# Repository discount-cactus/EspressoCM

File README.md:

# EspressoCM
Espresso Rev 4 CM, or just Espresso CM, is an STM32- and ESP32-based compute module for high performance networking and automation applications. The board was designed to provide a plethora of capabilities in a small, user-friendly and cheap package. An STM32 and two (not one but two!) ESP32's were chosen for their ease-of-use, clock speed and peripherals to acommodate these requirements. For the beginner or novel hobbyist, the ESP32's can be used - both come with their own dedicated flash memory chip as well as Wi-Fi and Bluetooth connectivity. For the more advanced and tech-savy, the STM32 can be programmed directly for higher-performance control.

Link to EspressoCM's complimentary library: https://github.com/discount-cactus/EspressoCMlib

## Board Statistics
- Dimensions: 84.9mm x 50.2mm
- Layers: 4
- Components: 83
- Mounting Hole Size: M2

## Features
- 1 x STM32F107 (@72MHz)
- 2 x ESP32-S3 (@240MHz)
- 1 x ATtiny85
- 1.5A linear regulator (VIN: 3-20V)
- Automatic power switchover from terminal block `J7` and JST battery connector `J8`
- JST LiPo Battery Connector
- 128Mbit Flash (one per ESP32)
- Dedicated E2B functionality
- On-board current sensing

## Applications
- Smart Homes
- Home networks
- IoT Connectivity
- Home automation
- Sensor monitoring

## Programming
### STM32
- The STM32 is programmed on-board via the pin connector `J5` with an ST-Link V2.
- Verify STM32CubeIDE is up-to-date
- Verify ST-Link V2 is up-to-date
1. Set BOOT0 to HIGH
2. Push reset button
3. Build code
4. Run code
5. Set BOOT0 to LOW
6. Push reset button

### ESP32
- The ESP32's are programmed on-board via the header pins `J3` (for Core 1) and `J4` (for Core 2). Pins are labeled on silkscreen.

### ATtiny85
- The ATtiny85 is programmed off-board.

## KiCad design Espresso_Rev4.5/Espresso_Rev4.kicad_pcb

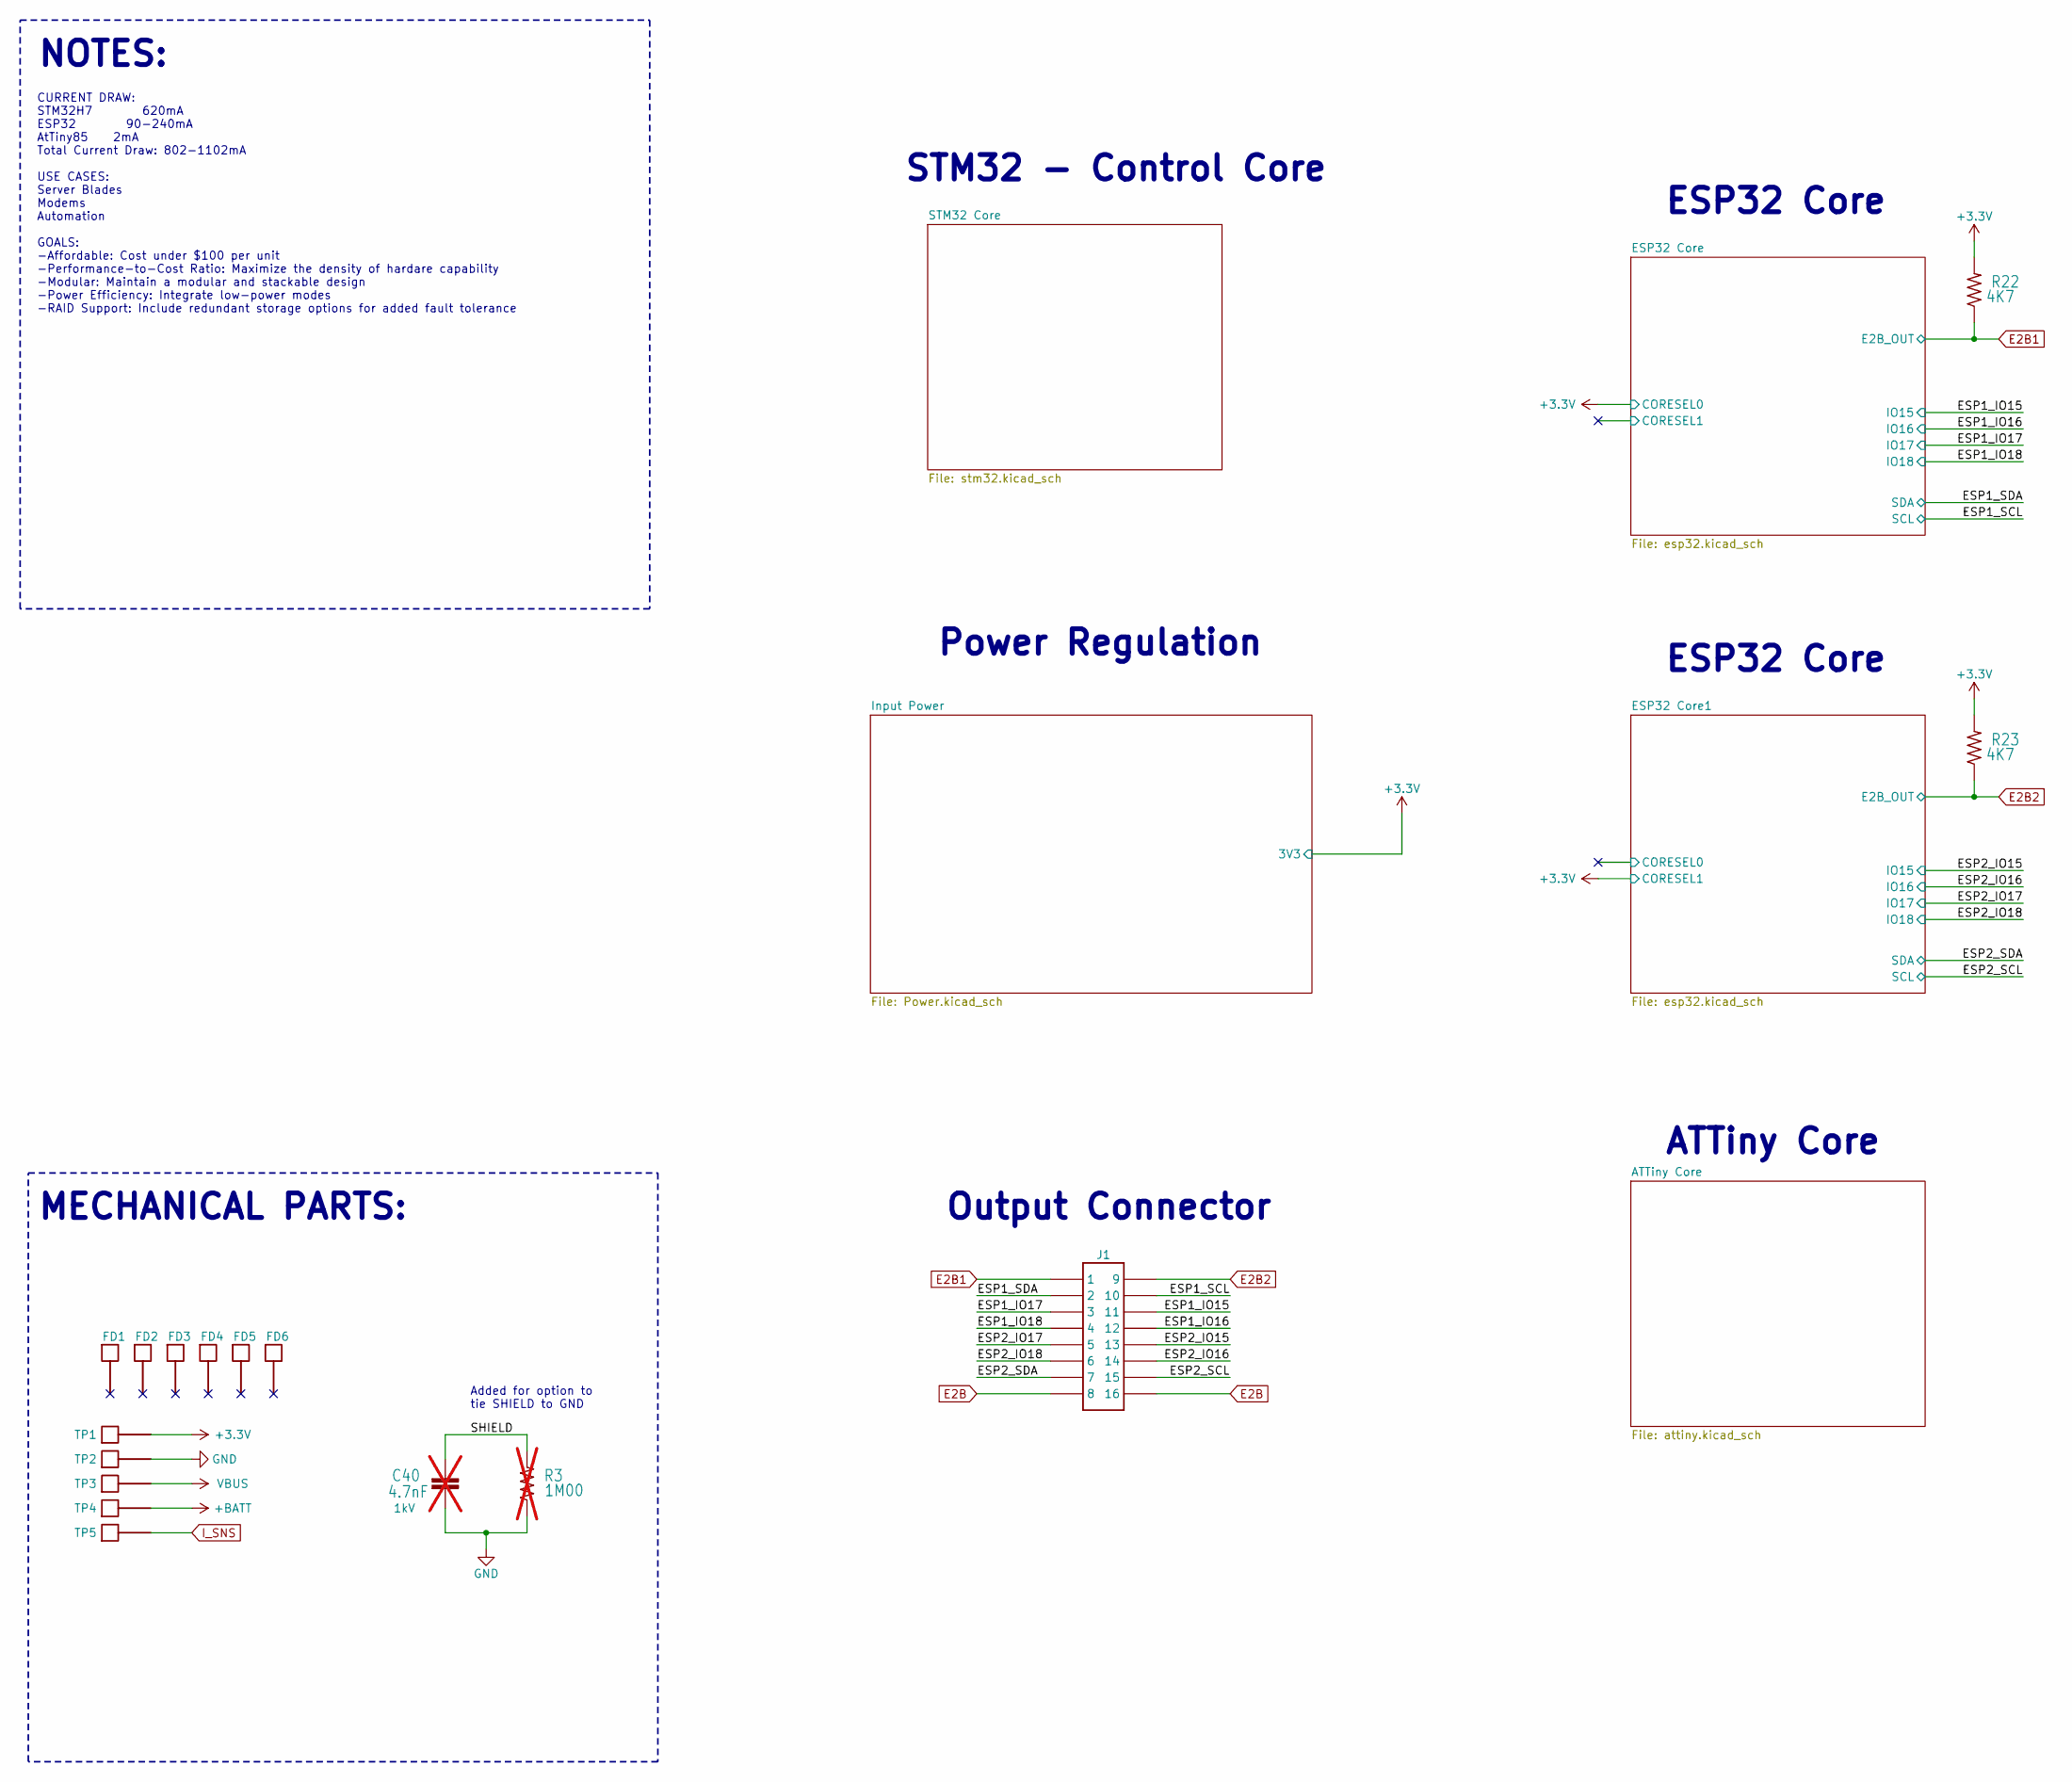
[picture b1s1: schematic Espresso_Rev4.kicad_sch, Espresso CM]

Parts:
C40: 4.7nF; C_1206; Rating 1kV; Part Number C1206C472KDRACAUTO; not fitted
FD1, FD2, FD3, FD4, FD5, FD6: Fiducial_1.5mm_Mask3mm
J1: 2X8; Part Number PPTC082LJBN-RC
R3: 1M00; R_1206; Rating 1/4W; Part Number RMCF1206FG1M00; not fitted
R22, R23: 4K7; R_1206; Rating 1/4W; Part Number RMCF1206FT4K70
TP1, TP2, TP3, TP4, TP5: TESTPOINT

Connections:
+3.3V: R22.2, R23.2, TP1.1; also elsewhere on the board
+BATT: TP4.1; also elsewhere on the board
/ESP1_IO15: J1.11; also elsewhere on the board
/ESP1_IO16: J1.12; also elsewhere on the board
/ESP1_IO17: J1.3; also elsewhere on the board
/ESP1_IO18: J1.4; also elsewhere on the board
/ESP1_SCL: J1.10; also elsewhere on the board
/ESP1_SDA: J1.2; also elsewhere on the board
/ESP2_IO15: J1.13; also elsewhere on the board
/ESP2_IO16: J1.14; also elsewhere on the board
/ESP2_IO17: J1.5; also elsewhere on the board
/ESP2_IO18: J1.6; also elsewhere on the board
/ESP2_SCL: J1.15; also elsewhere on the board
/ESP2_SDA: J1.7; also elsewhere on the board
/SHIELD: C40.1, R3.2; also elsewhere on the board
E2B: J1.8, J1.16; also elsewhere on the board
E2B1: J1.1, R22.1; also elsewhere on the board
E2B2: J1.9, R23.1; also elsewhere on the board
GND: C40.2, R3.1, TP2.1; also elsewhere on the board
I_SNS: TP5.1; also elsewhere on the board
VBUS: TP3.1; also elsewhere on the board

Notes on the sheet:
MECHANICAL PARTS:
Power Regulation
Added for option to tie SHIELD to GND
Output Connector
ESP32 Core
NOTES:
CURRENT DRAW: STM32H7 620mA ESP32 90-240mA AtTiny85 2mA Total Current Draw: 802-1102mA USE CASES: Server Blades Modems Automation GOALS: -Affordable: Cost under $100 per unit -Performance-to-Cost Ratio: Maximize the density of hardare capability -Modular: Maintain a modular and stackable design -Po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
ATTiny Core
STM32 - Control Core

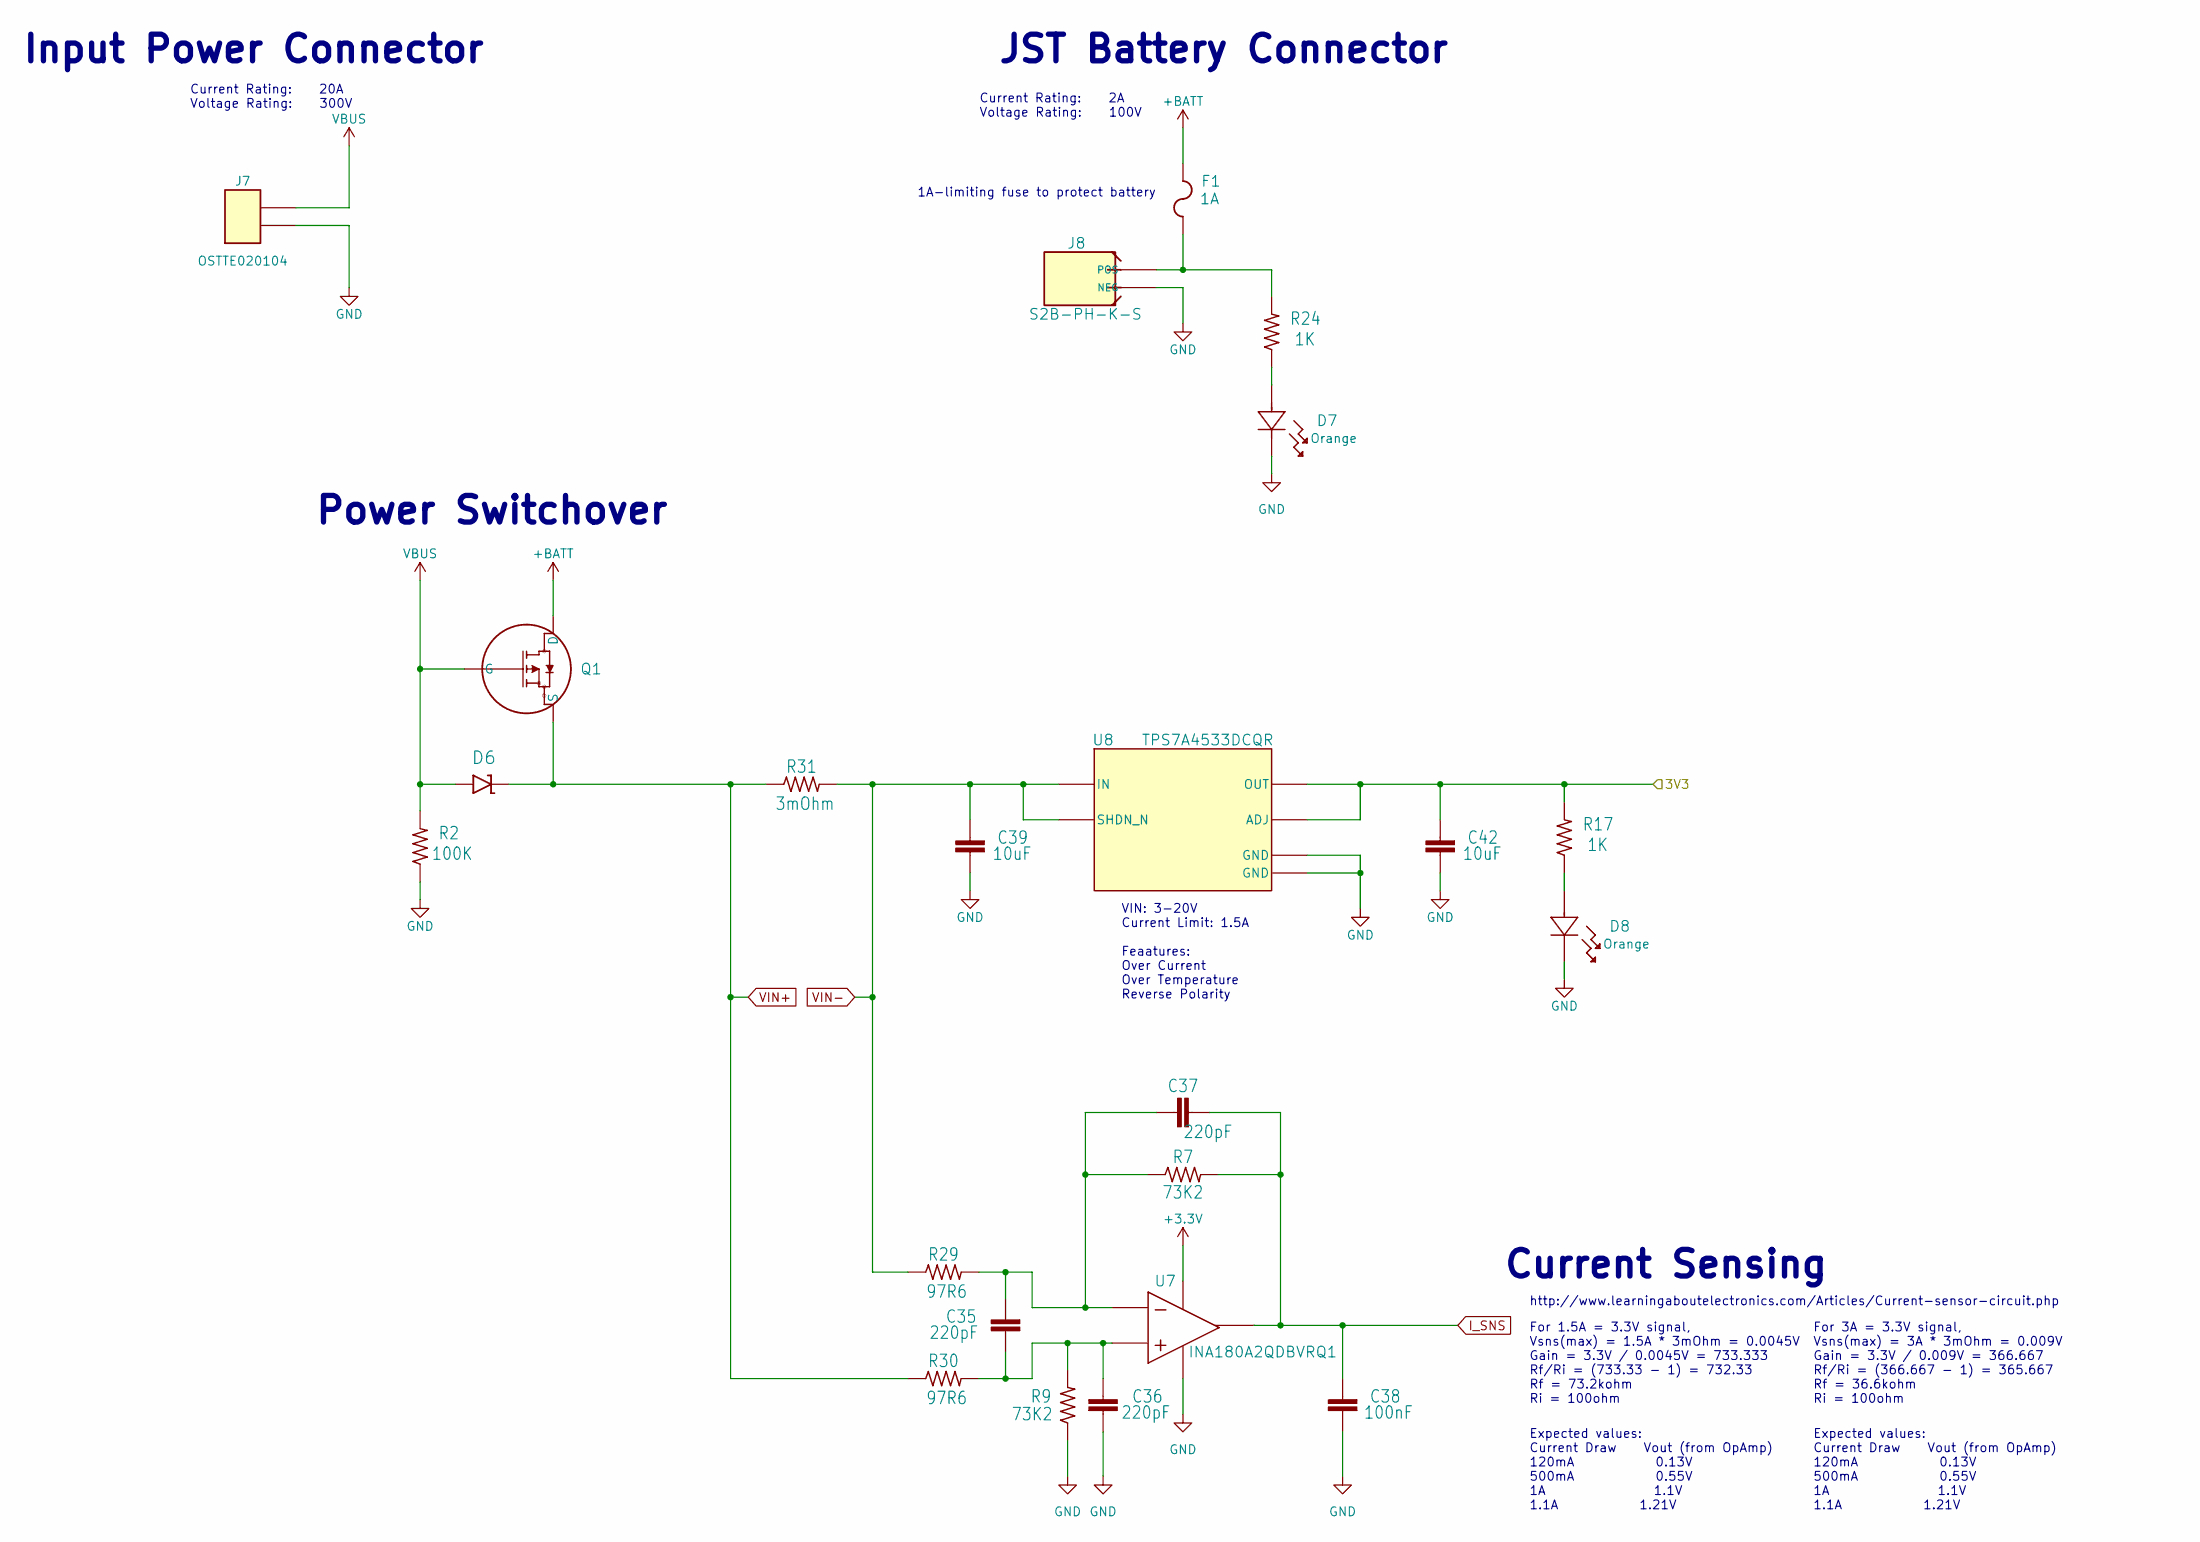
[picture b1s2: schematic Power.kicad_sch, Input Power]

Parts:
C35, C36, C37: 220pF; C_0603; Rating 50V; Part Number CL10B221KB8NFNC
C38: 100nF; C_0603; Rating 50V; Part Number CL10B104KB8NNNC
C39, C42: 10uF; C_0603; Rating 25V; Part Number CL10A106MA8NRNC
D6: SK54AHE3-LTP; Part Number SK54AHE3-LTP
D7, D8: LED_0603; Part Number LTST-C191KFKT
F1: 1A; MF-FSMF050X-2; Part Number MF-FSMF050X-2
J7: OSTTE020104; Rating 10A; Part Number OSTTE020104
J8: S2B-PH-K-S; Part Number S2B-PH-K-S
Q1: DMP3099L-7; Part Number DMP3099L-7
R2: 100K; R_0603; Rating 1/10W; Part Number RMCF0603FT100K
R7, R9: 73K2; R_0603; Rating 1/10W; Part Number RMCF0603FT73K2
R17, R24: 1K; R_0603; Rating 1/10W; Part Number RMCF0603FT1K00
R29, R30: 97R6; R_1206; Rating 1/4W; Part Number RK73H2BTTD97R6F
R31: 3mOhm; R_1206; Rating 1W; Part Number PMR18EZPFV3L00
U7: INA180A2QDBVRQ1; Part Number INA180A2QDBVRQ1
U8: TPS7A4533DCQR; Part Number TPS7A4533DCQR

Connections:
+3.3V: C42.2, R17.2, U7.5 (V+), U8.4 (OUT), U8.5 (ADJ); also elsewhere on the board
+BATT: F1.2, Q1.3 (D); also elsewhere on the board
GND: C36.1, C38.1, C39.1, C42.1, D7.1, D8.1, J7.1, J8.2 (NEG), R2.1, R9.1, U7.2 (V-), U8.3 (GND), U8.6 (GND); also elsewhere on the board
I_SNS: C37.2, C38.2, R7.2, U7.1 (OUT); also elsewhere on the board
unnamed: D7.2, R24.1
unnamed: D8.2, R17.1
unnamed: F1.1, J8.1 (POS), R24.2
unnamed: C35.1, C36.2, R9.2, R30.2, U7.3 (IN+)
unnamed: C35.2, C37.1, R7.1, R29.2, U7.4 (IN-)
VBUS: D6.2, J7.2, Q1.1 (G), R2.2; also elsewhere on the board
VIN+: D6.1, Q1.2 (S), R30.1, R31.1
VIN-: C39.2, R29.1, R31.2, U8.1 (SHDN_N), U8.2 (IN)

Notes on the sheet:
http://www.learningaboutelectronics.com/Articles/Current-sensor-circuit.php
VIN: 3-20V Current Limit: 1.5A Feaatures: Over Current Over Temperature Reverse Polarity
1A-limiting fuse to protect battery
Expected values: Current Draw Vout (from OpAmp) 120mA 0.13V 500mA 0.55V 1A 1.1V 1.1A 1.21V
For 1.5A = 3.3V signal, Vsns(max) = 1.5A * 3mOhm = 0.0045V Gain = 3.3V / 0.0045V = 733.333 Rf/Ri = (733.33 - 1) = 732.33 Rf = 73.2kohm Ri = 100ohm
Power Switchover
For 3A = 3.3V signal, Vsns(max) = 3A * 3mOhm = 0.009V Gain = 3.3V / 0.009V = 366.667 Rf/Ri = (366.667 - 1) = 365.667 Rf = 36.6kohm Ri = 100ohm
Current Rating: 2A Voltage Rating: 100V
Current Rating: 20A Voltage Rating: 300V
JST Battery Connector
Current Sensing
Input Power Connector

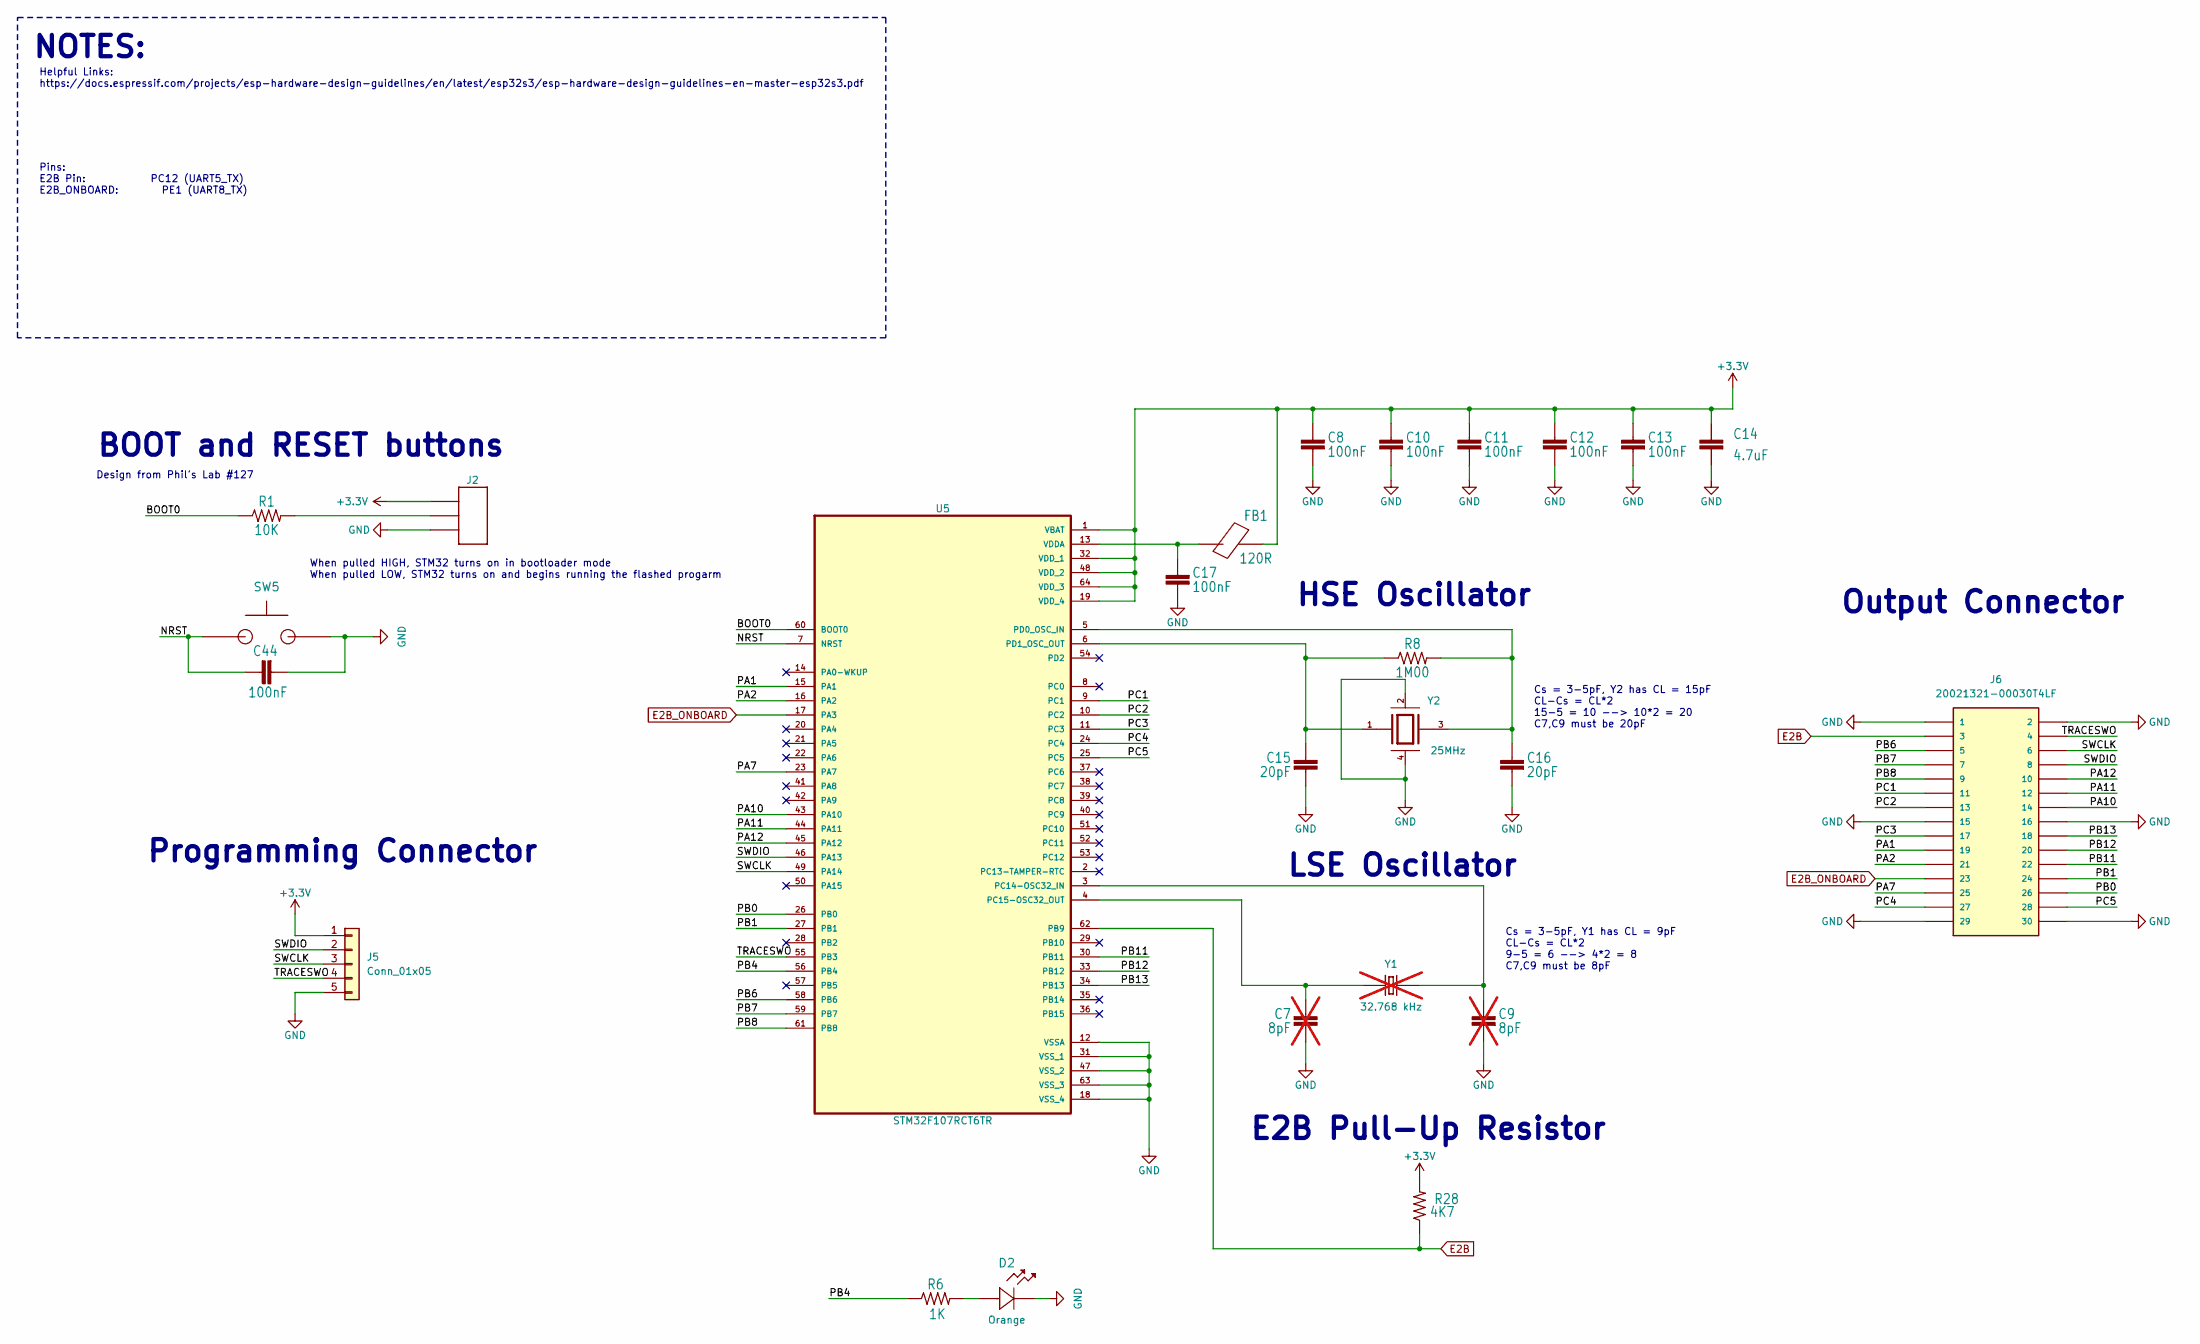
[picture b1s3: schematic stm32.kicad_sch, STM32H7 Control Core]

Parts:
C7, C9: 8pF; C_0603; Rating 50V; Part Number CL10C080DB81PNC; not fitted
C8, C10, C11, C12, C13, C17, C44: 100nF; C_0603; Rating 50V; Part Number CL10B104KB8NNNC
C14: 4.7uF; C_0603; Rating 25V; Part Number CL10A475MA8NQNC
C15, C16: 20pF; C_0603; Rating 50V; Part Number CL10C200JB8NNNC
D2: LED_0603; Part Number LTST-C191KFKT
FB1: 120R; FB_0603; Part Number BLM18KG121TN1D
J2: 1X3
J5: Conn_01x05; PinHeader_1x05_P2.54mm_Vertical
J6: 20021321-00030T4LF; Part Number 20021321-00030T4LF
R1: 10K; R_0603; Rating 1/10W; Part Number RMCF0603FT10K0
R6: 1K; R_0603; Rating 1/10W; Part Number RMCF0603FT1K00
R8: 1M00; R_0603; Rating 1/10W; Part Number RMCF0603FT1M00
R28: 4K7; R_1206; Rating 1/4W; Part Number RMCF1206FT4K70
SW5: PTS636 SK25J SMTR LFS; Part Number PTS636SK25JSMTR LFS
U5: STM32F107RCT6TR; Part Number STM32F107RCT6TR
Y1: 32.768 kHz; ECS-.327-9-34B-TR; Part Number ECS-.327-9-34B-TR; not fitted
Y2: 25MHz; ECS-2333-250-BN-TR; Part Number ECS-2333-250-BN-TR

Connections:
+3.3V: C8.2, C10.2, C11.2, C12.2, C13.2, C14.2, FB1.2, J2.1, J5.1, R28.2, U5.1 (VBAT), U5.19 (VDD_4), U5.32 (VDD_1), U5.48 (VDD_2), U5.64 (VDD_3); also elsewhere on the board
/STM32 Core/BOOT0: R1.1, U5.60 (BOOT0)
/STM32 Core/NRST: C44.2, SW5.1, U5.7 (NRST)
/STM32 Core/PA1: J6.19, U5.15 (PA1)
/STM32 Core/PA2: J6.21, U5.16 (PA2)
/STM32 Core/PA7: J6.25, U5.23 (PA7)
/STM32 Core/PA10: J6.14, U5.43 (PA10)
/STM32 Core/PA11: J6.12, U5.44 (PA11)
/STM32 Core/PA12: J6.10, U5.45 (PA12)
/STM32 Core/PB0: J6.26, U5.26 (PB0)
/STM32 Core/PB1: J6.24, U5.27 (PB1)
/STM32 Core/PB4: R6.1, U5.56 (PB4)
/STM32 Core/PB6: J6.5, U5.58 (PB6)
/STM32 Core/PB7: J6.7, U5.59 (PB7)
/STM32 Core/PB8: J6.9, U5.61 (PB8)
/STM32 Core/PB11: J6.22, U5.30 (PB11)
/STM32 Core/PB12: J6.20, U5.33 (PB12)
/STM32 Core/PB13: J6.18, U5.34 (PB13)
/STM32 Core/PC1: J6.11, U5.9 (PC1)
/STM32 Core/PC2: J6.13, U5.10 (PC2)
/STM32 Core/PC3: J6.17, U5.11 (PC3)
/STM32 Core/PC4: J6.27, U5.24 (PC4)
/STM32 Core/PC5: J6.28, U5.25 (PC5)
/STM32 Core/SWCLK: J5.3, J6.6, U5.49 (PA14)
/STM32 Core/SWDIO: J5.2, J6.8, U5.46 (PA13)
/STM32 Core/TRACESWO: J5.4, J6.4, U5.55 (PB3)
E2B: J6.3, R28.1, U5.62 (PB9); also elsewhere on the board
E2B_ONBOARD: J6.23, U5.17 (PA3); also elsewhere on the board
GND: C7.1, C8.1, C9.1, C10.1, C11.1, C12.1, C13.1, C14.1, C15.1, C16.1, C17.1, C44.1, D2.1, J2.3, J5.5, J6.1, J6.2, J6.15, J6.16, J6.29, J6.30, SW5.2, U5.12 (VSSA), U5.18 (VSS_4), U5.31 (VSS_1), U5.47 (VSS_2), U5.63 (VSS_3), Y2.2 (GND), Y2.4 (GND); also elsewhere on the board
unnamed: D2.2, R6.2
unnamed: J2.2, R1.2
unnamed: C9.2, U5.3 (PC14-OSC32_IN), Y1.2
unnamed: C7.2, U5.4 (PC15-OSC32_OUT), Y1.1
unnamed: C16.2, R8.2, U5.5 (PD0_OSC_IN), Y2.3 (OUT)
unnamed: C15.2, R8.1, U5.6 (PD1_OSC_OUT), Y2.1 (IN)
unnamed: C17.2, FB1.1, U5.13 (VDDA)

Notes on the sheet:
HSE Oscillator
E2B Pull-Up Resistor
Pins: E2B Pin: PC12 (UART5_TX) E2B_ONBOARD: PE1 (UART8_TX)
Design from Phil's Lab #127
Output Connector
NOTES:
When pulled HIGH, STM32 turns on in bootloader mode When pulled LOW, STM32 turns on and begins running the flashed progarm
LSE Oscillator
Cs = 3-5pF, Y2 has CL = 15pF CL-Cs = CL*2 15-5 = 10 --> 10*2 = 20 C7,C9 must be 20pF
Cs = 3-5pF, Y1 has CL = 9pF CL-Cs = CL*2 9-5 = 6 --> 4*2 = 8 C7,C9 must be 8pF
Programming Connector
BOOT and RESET buttons
Helpful Links: https://docs.espressif.com/projects/esp-hardware-design-guidelines/en/latest/esp32s3/esp-hardware-design-guidelines-en-master-esp32s3.pdf

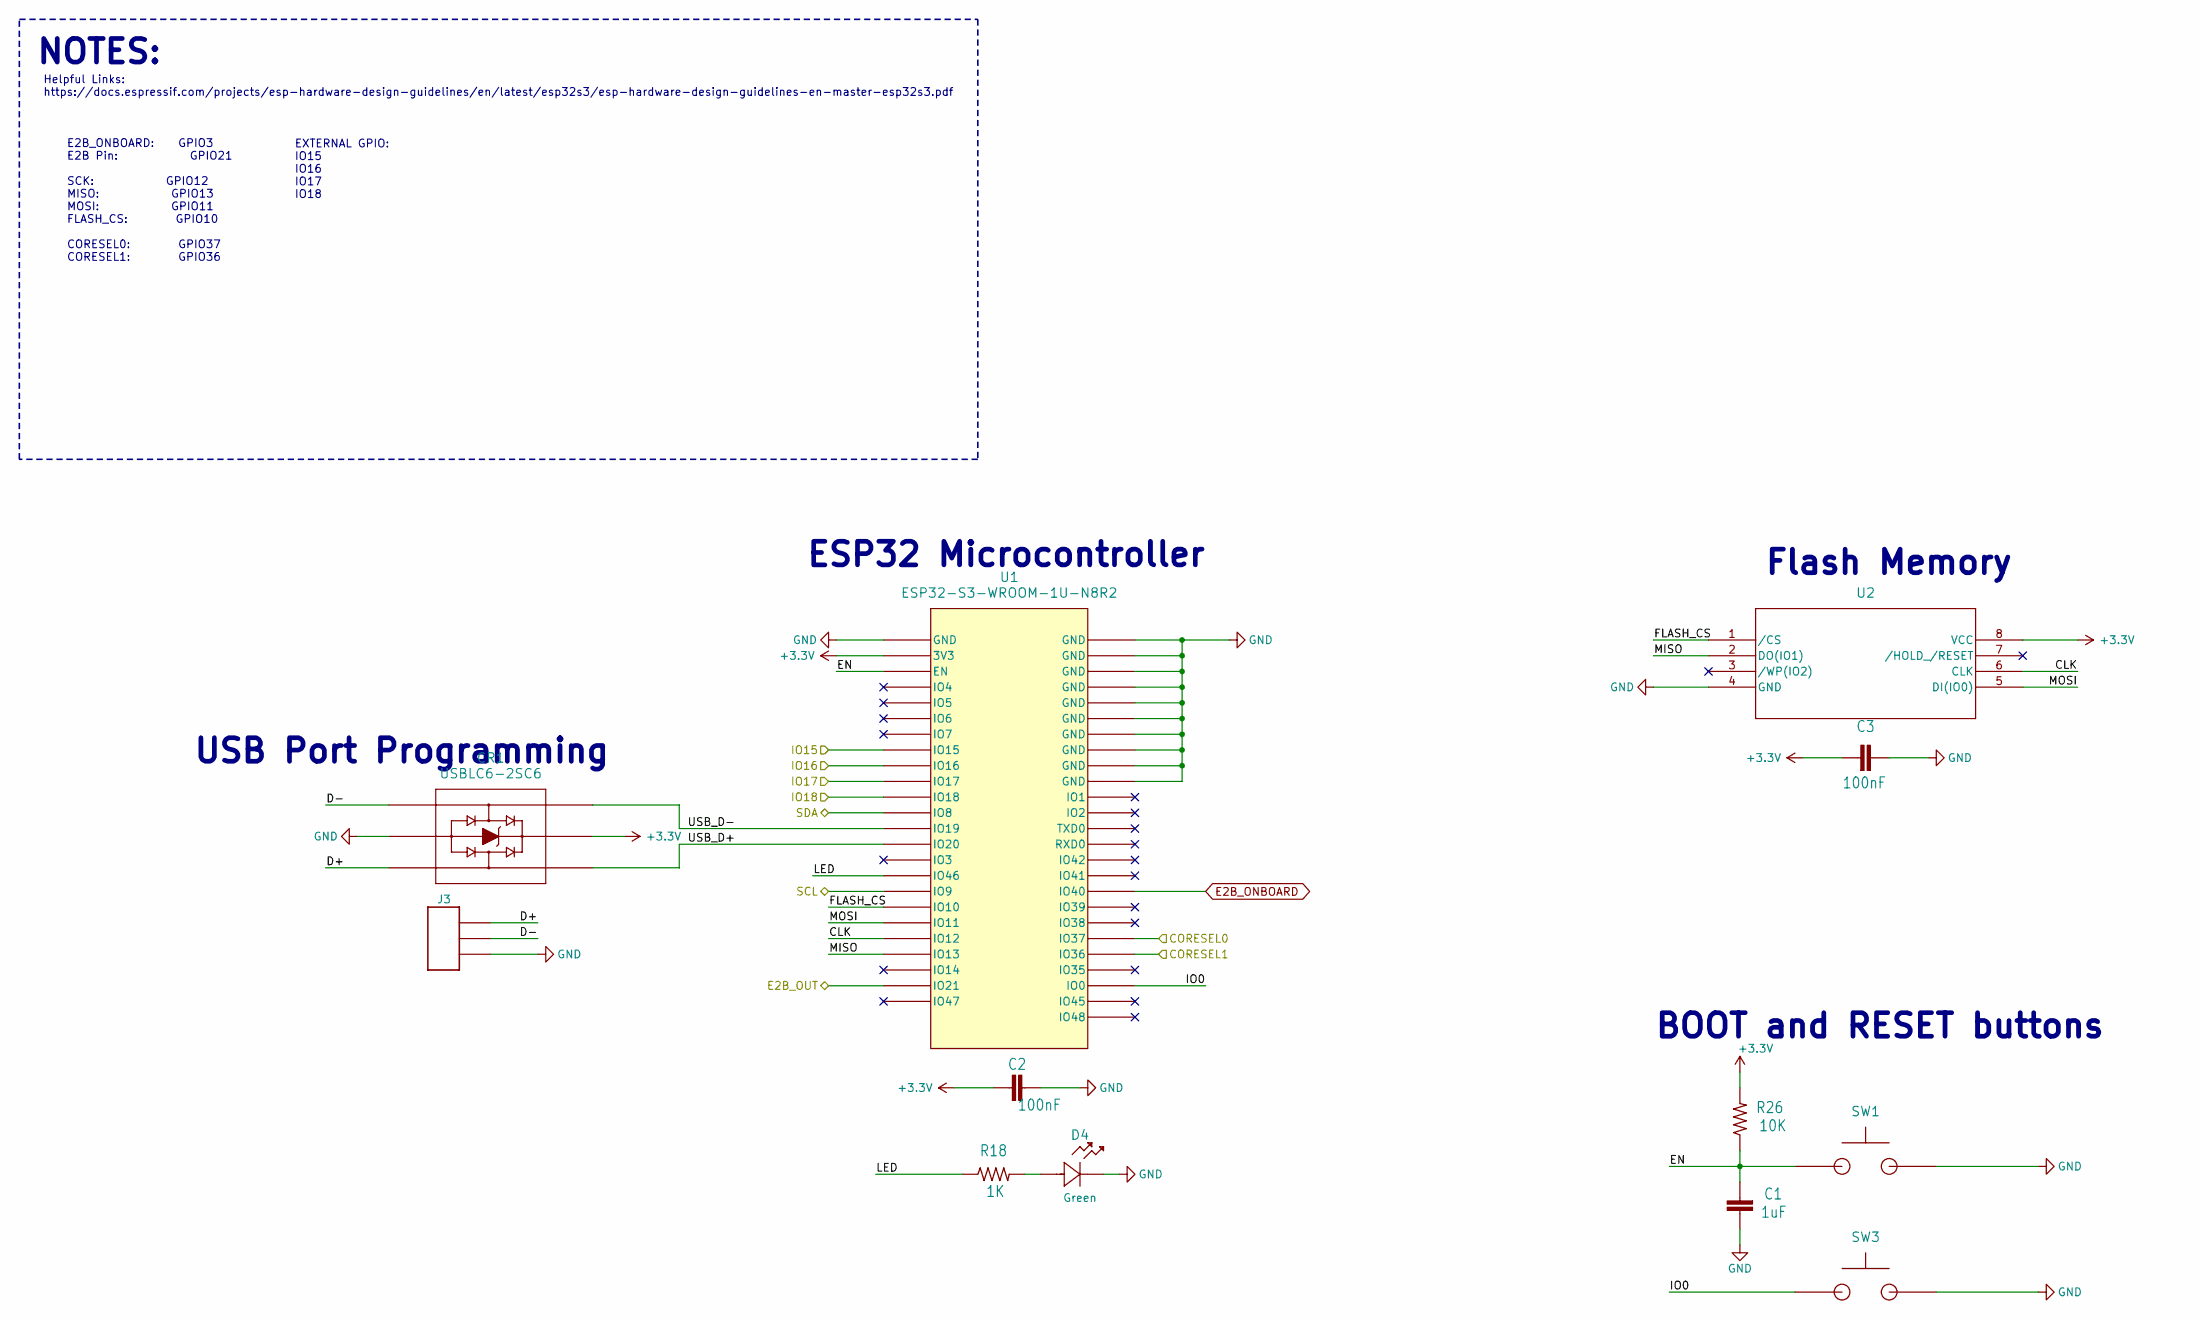
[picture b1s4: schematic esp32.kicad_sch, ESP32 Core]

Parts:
C1: 1uF; C_0603; Rating 50V; Part Number CL10A105KB8NNNC
C2, C3: 100nF; C_0603; Rating 50V; Part Number CL10B104KB8NNNC
CR1: USBLC6-2SC6; Part Number USBLC6-2SC6
D4: LED_0603; Part Number LTST-C191KGKT
J3: 1X3
R18: 1K; R_0603; Rating 1/10W; Part Number RMCF0603FT1K00
R26: 10K; R_0603; Rating 1/10W; Part Number RMCF0603FT10K0
SW1, SW3: PTS636 SK25J SMTR LFS; Part Number PTS636SK25JSMTR LFS
U1: ESP32-S3-WROOM-1U-N8R2; Part Number ESP32-S3-WROOM-1U-N8R2
U2: W25Q128JVSIQ; Part Number W25Q128JVSIQ

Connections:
+3.3V: C2.1, C3.1, CR1.5, R26.2, U1.2 (3V3), U1.30 (IO37), U2.8 (VCC); also elsewhere on the board
/ESP1_IO15: U1.8 (IO15); also elsewhere on the board
/ESP1_IO16: U1.9 (IO16); also elsewhere on the board
/ESP1_IO17: U1.10 (IO17); also elsewhere on the board
/ESP1_IO18: U1.11 (IO18); also elsewhere on the board
/ESP1_SCL: U1.17 (IO9); also elsewhere on the board
/ESP1_SDA: U1.12 (IO8); also elsewhere on the board
/ESP32 Core/CLK: U1.20 (IO12), U2.6 (CLK)
/ESP32 Core/CORESEL1: U1.29 (IO36)
/ESP32 Core/D+: CR1.3, J3.1
/ESP32 Core/D-: CR1.1, J3.2
/ESP32 Core/EN: C1.2, R26.1, SW1.1, U1.3 (EN)
/ESP32 Core/FLASH_CS: U1.18 (IO10), U2.1 (/CS)
/ESP32 Core/IO0: SW3.1, U1.27 (IO0)
/ESP32 Core/LED: R18.1, U1.16 (IO46)
/ESP32 Core/MISO: U1.21 (IO13), U2.2 (DO(IO1))
/ESP32 Core/MOSI: U1.19 (IO11), U2.5 (DI(IO0))
/ESP32 Core/USB_D+: CR1.4, U1.14 (IO20)
/ESP32 Core/USB_D-: CR1.6, U1.13 (IO19)
E2B1: U1.23 (IO21); also elsewhere on the board
E2B_ONBOARD: U1.33 (IO40); also elsewhere on the board
GND: C1.1, C2.2, C3.2, CR1.2, D4.1, J3.3, SW1.2, SW3.2, U1.1 (GND), U1.40 (GND), U1.41 (GND), U1.42 (GND), U1.43 (GND), U1.44 (GND), U1.45 (GND), U1.46 (GND), U1.47 (GND), U1.48 (GND), U1.49 (GND), U2.4 (GND); also elsewhere on the board
unnamed: D4.2, R18.2

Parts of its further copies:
C4: 1uF; C_0603; Rating 50V; Part Number CL10A105KB8NNNC
C5, C6: 100nF; C_0603; Rating 50V; Part Number CL10B104KB8NNNC
CR2: USBLC6-2SC6; Part Number USBLC6-2SC6
D5: LED_0603; Part Number LTST-C191KGKT
J4: 1X3
R25: 1K; R_0603; Rating 1/10W; Part Number RMCF0603FT1K00
R27: 10K; R_0603; Rating 1/10W; Part Number RMCF0603FT10K0
SW2, SW4: PTS636 SK25J SMTR LFS; Part Number PTS636SK25JSMTR LFS
U3: ESP32-S3-WROOM-1U-N8R2; Part Number ESP32-S3-WROOM-1U-N8R2
U4: W25Q128JVSIQ; Part Number W25Q128JVSIQ

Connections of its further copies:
+3.3V: C5.1, C6.1, CR2.5, R27.2, U3.2 (3V3), U3.29 (IO36), U4.8 (VCC); also elsewhere on the board
/ESP2_IO15: U3.8 (IO15); also elsewhere on the board
/ESP2_IO16: U3.9 (IO16); also elsewhere on the board
/ESP2_IO17: U3.10 (IO17); also elsewhere on the board
/ESP2_IO18: U3.11 (IO18); also elsewhere on the board
/ESP2_SCL: U3.17 (IO9); also elsewhere on the board
/ESP2_SDA: U3.12 (IO8); also elsewhere on the board
/ESP32 Core1/CLK: U3.20 (IO12), U4.6 (CLK)
/ESP32 Core1/CORESEL0: U3.30 (IO37)
/ESP32 Core1/D+: CR2.3, J4.1
/ESP32 Core1/D-: CR2.1, J4.2
/ESP32 Core1/EN: C4.2, R27.1, SW2.1, U3.3 (EN)
/ESP32 Core1/FLASH_CS: U3.18 (IO10), U4.1 (/CS)
/ESP32 Core1/IO0: SW4.1, U3.27 (IO0)
/ESP32 Core1/LED: R25.1, U3.16 (IO46)
/ESP32 Core1/MISO: U3.21 (IO13), U4.2 (DO(IO1))
/ESP32 Core1/MOSI: U3.19 (IO11), U4.5 (DI(IO0))
/ESP32 Core1/USB_D+: CR2.4, U3.14 (IO20)
/ESP32 Core1/USB_D-: CR2.6, U3.13 (IO19)
E2B2: U3.23 (IO21); also elsewhere on the board
E2B_ONBOARD: U3.33 (IO40); also elsewhere on the board
GND: C4.1, C5.2, C6.2, CR2.2, D5.1, J4.3, SW2.2, SW4.2, U3.1 (GND), U3.40 (GND), U3.41 (GND), U3.42 (GND), U3.43 (GND), U3.44 (GND), U3.45 (GND), U3.46 (GND), U3.47 (GND), U3.48 (GND), U3.49 (GND), U4.4 (GND); also elsewhere on the board
unnamed: D5.2, R25.2

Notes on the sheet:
E2B_ONBOARD: GPIO3 E2B Pin: GPIO21 SCK: GPIO12 MISO: GPIO13 MOSI: GPIO11 FLASH_CS: GPIO10 CORESEL0: GPIO37 CORESEL1: GPIO36
EXTERNAL GPIO: IO15 IO16 IO17 IO18
BOOT and RESET buttons
NOTES:
Helpful Links: https://docs.espressif.com/projects/esp-hardware-design-guidelines/en/latest/esp32s3/esp-hardware-design-guidelines-en-master-esp32s3.pdf
Flash Memory
ESP32 Microcontroller
USB Port Programming

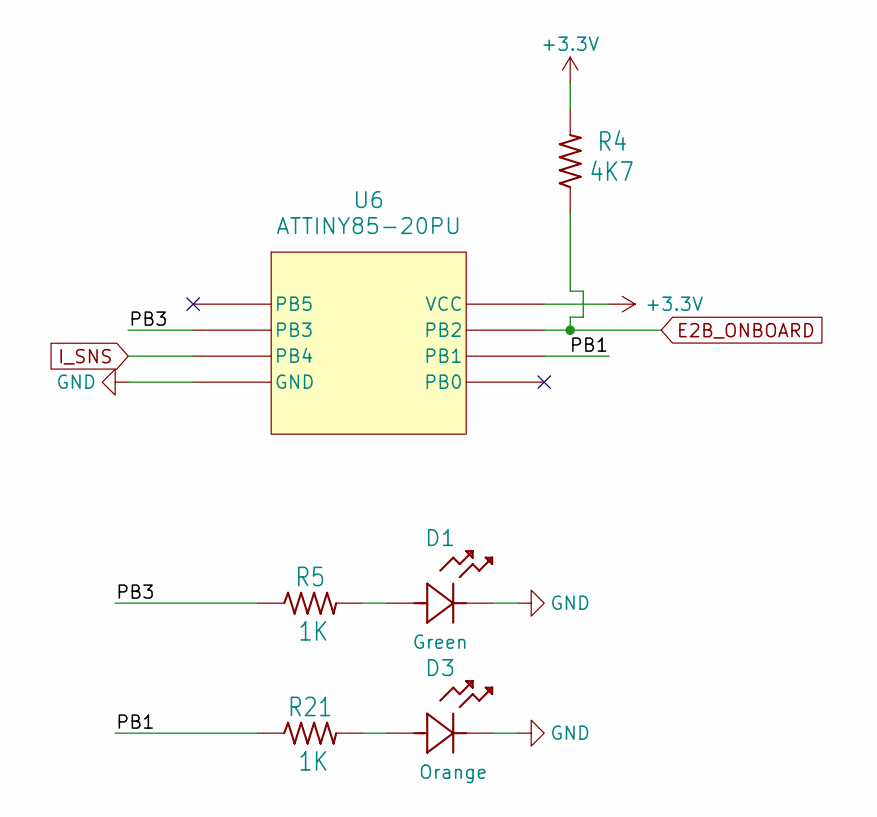
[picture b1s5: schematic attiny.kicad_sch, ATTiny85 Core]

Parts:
D1: LED_0603; Part Number LTST-C191KGKT
D3: LED_0603; Part Number LTST-C191KFKT
R4: 4K7; R_1206; Rating 1/4W; Part Number RMCF1206FT4K70
R5, R21: 1K; R_0603; Rating 1/10W; Part Number RMCF0603FT1K00
U6: ATTINY85-20PU; Part Number ATTINY85-20PU

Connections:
+3.3V: R4.2, U6.8 (VCC); also elsewhere on the board
/ATTiny Core/PB1: R21.1, U6.6 (PB1)
/ATTiny Core/PB3: R5.1, U6.2 (PB3)
E2B_ONBOARD: R4.1, U6.7 (PB2); also elsewhere on the board
GND: D1.1, D3.1, U6.4 (GND); also elsewhere on the board
I_SNS: U6.3 (PB4); also elsewhere on the board
unnamed: D1.2, R5.2
unnamed: D3.2, R21.2
